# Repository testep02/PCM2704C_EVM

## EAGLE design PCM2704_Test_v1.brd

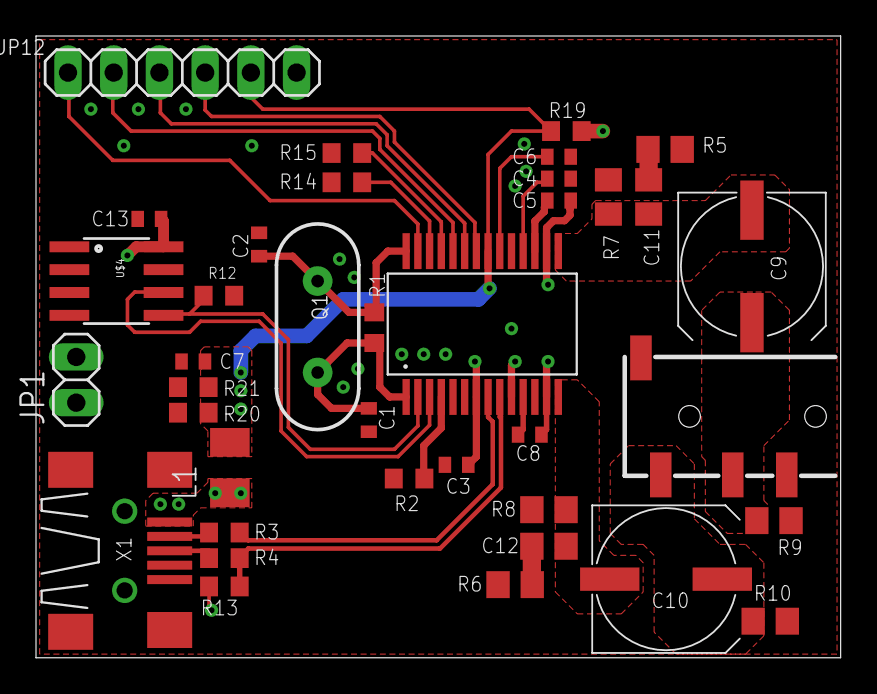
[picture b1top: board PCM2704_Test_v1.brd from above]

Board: 2 copper layers, 44.7 x 34.5 mm, 39 parts (1 on the bottom side), 28 nets.

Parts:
C1, C2, C3, C4, C5, C6, C7, C8, C13: 1u; C0402
C9, C10: 100u; UD-8X10_NICHICON
C11, C12: 10u; C0805
IC1: LT1963EFE-3.3; TSSOP16
JP1: 1X02
JP12: 1X06
L1: L3225M
Q1: HC49US
R1: 1M; R0603
R2, R12, R13, R14, R15, R19, R20, R21: 1k5; R0603
R3, R4: 22; R0603
R5, R6, R7, R8, R9, R10: 1k5; R0805
U$1: PCM2704C
U$2: AUDIO-JACK3; AUDIO-JACK-TRRS-SMD
U$4: EEPROM-I2CSMD; SO08
X1: USB-MB-S

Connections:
D_N: R3.2, U$1.8
D_P: R4.2, R13.1, U$1.9
GND: C1.2, C2.2, C3.1, C4.2, C5.1, C6.2, C7.2, C8.2, C13.2, IC1.1, IC1.7, IC1.8, IC1.9, IC1.15, JP1.2, JP12.6, R2.2, R5.1, R6.1, R7.1, R8.1, R9.1, R10.1, R20.1, R21.1, U$1.6, U$1.11, U$1.12, U$1.17, U$1.19, U$2.RING2, U$4.1, U$4.2, U$4.3, U$4.4, U$4.7, X1.GND
HP_OUT_L: C10.+, R10.2, U$2.TIP
HP_OUT_R: C9.+, R9.2, U$2.RING1
unnamed: C1.1, Q1.1, R1.1, U$1.1
unnamed: C2.1, Q1.2, R1.2, U$1.28
unnamed: IC1.12, IC1.13, IC1.14, JP1.1
unnamed: JP12.2, U$1.24
unnamed: R2.1, U$1.4
unnamed: JP12.3, U$1.23
unnamed: JP12.4, U$1.22
unnamed: C6.1, U$1.20
unnamed: R14.1, U$1.26
unnamed: R15.1, U$1.25
unnamed: R12.1, U$1.2, U$4.5
unnamed: U$1.3, U$4.6
unnamed: C4.1, U$1.18
unnamed: C11.2, R5.2
unnamed: C12.2, R6.2
SSPND: JP12.1, U$1.27
USB_D_N: R3.1, X1.D-
USB_D_P: R4.1, X1.D+
VBUS: C7.1, JP12.5, L1.2, R19.1, R20.2, R21.2, U$1.21
VBUS_RAW: L1.1, X1.VBUS
VDD: C3.2, C5.2, C8.1, C13.1, IC1.3, IC1.4, IC1.5, R12.2, R13.2, R14.2, R15.2, R19.2, U$1.7, U$1.10, U$1.13, U$1.16, U$4.8
VOUTL: C10.-, C12.1, R8.2, U$1.14
VOUTR: C9.-, C11.1, R7.2, U$1.15

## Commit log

2014-08-19 :lollipop: Added .gitattributes & .gitignore files
2014-08-19 Initial Checkin
    Incomplete board, but the schematic should be good to go.
    This schematic is for a self-powerd version.
2014-08-19 Removed Voltage Regulators
    For VBUS operation, no voltage regulators are required. I removed both
    of them from the board along with all supporting components such as
    filter caps, etc.
2014-08-19 Small changes made
    Wired up the SDA and SCL for the EEPROM. Also added a bypass cap to the
    EEPROM.
2014-08-20 Removed unnecessary components
    Removed:
    - Function Buttons
    - Resistors associated with the buttons
    Moved some components around to make better use of the space on the
    board. Decreased the board length and width. Routed the EEPROM traces
    and added a bypass capacitor footprint to the power pin of the EEPROM.
2014-08-20 Added LDO for Self-Power
    Added an LDO to this design for self-powering the board.
2014-08-21 Completed HP Traces
    Completed the polygon pour for the headphone jack traces.
2014-08-22 Ran power traces
    Ran power traces and moves some components to make room for the power.
    Rearranged some resistors to optimize the layout.
2014-08-26 Completed Board
    The board is now complete and ready for printing as soon as it is
    reviewed.
2014-08-27 Completed board
    Tested some changes, then removed them. Board is ready for printing
    after it is reviewed for accuracy and errors.
2014-08-27 Revert "Completed board"
    This reverts commit 0f96bb123a9a48b22ee927d277ee47eab9910a66.
2014-08-27 Completed board
    Made some changes to test, then removed them. Board is ready for
    printing as soon as it is reviewed for accuracy and errors. Also needs
    to have DRC run on it to ensure all specs are within tolerance.

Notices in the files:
parts and their libraries:
SparkFun-Connectors: Licensing: CC v3.0 Share-Alike You are welcome to use this library for commercial purposes.
